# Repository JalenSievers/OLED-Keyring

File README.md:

# OLED-Keyring
A custom-designed OLED keyring featuring an ATmega4808 microcontroller, compact PCB, and embedded firmware for displaying personalised messages and simple games.

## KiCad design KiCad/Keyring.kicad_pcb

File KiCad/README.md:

KiCad schematic and PCB design files for the OLED keyring project.

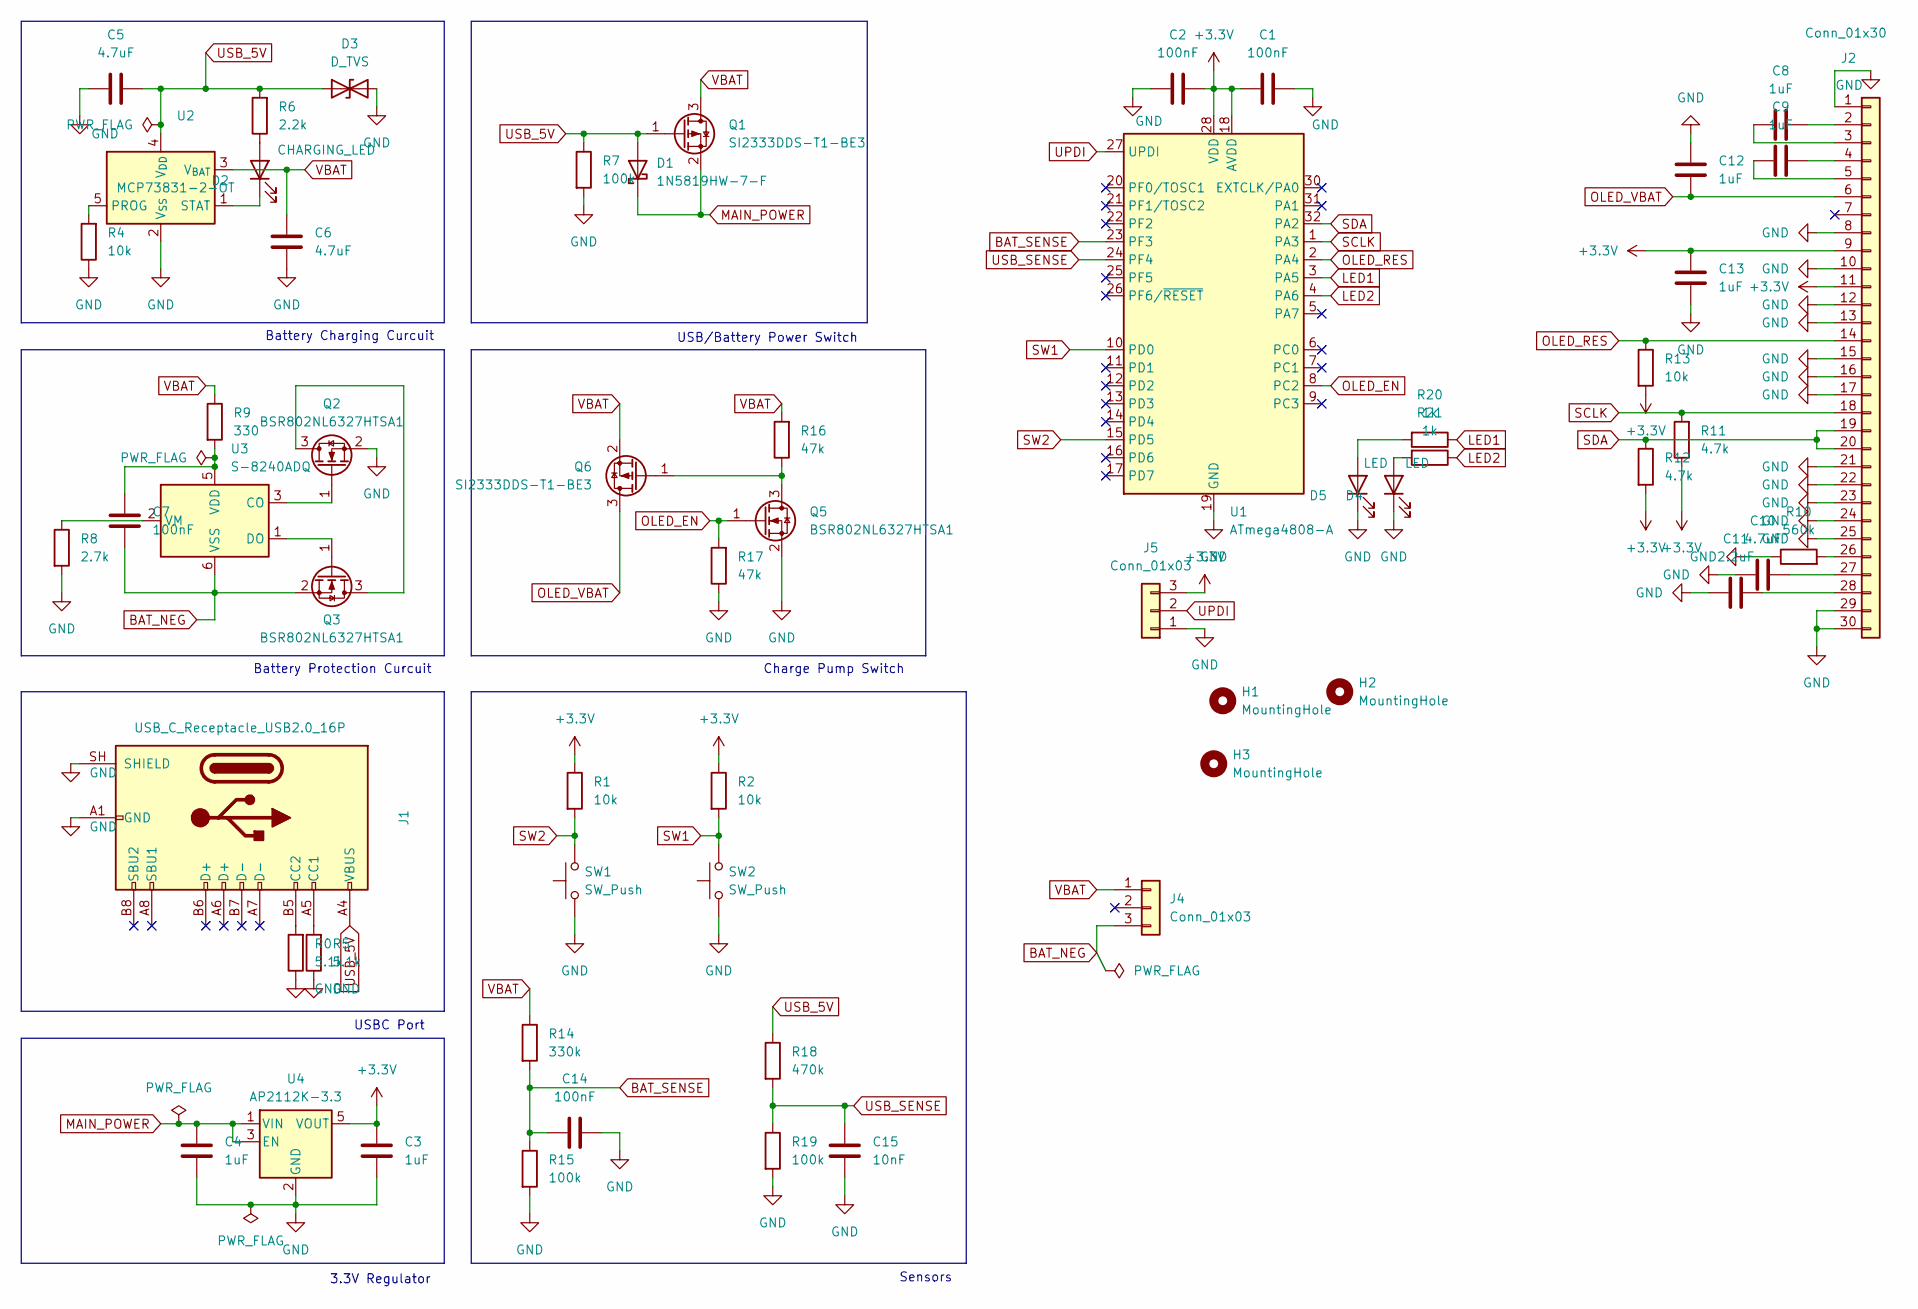
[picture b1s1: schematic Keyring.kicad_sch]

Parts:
C1, C2, C7, C14: 100nF; C_0805_2012Metric_Pad1.18x1.45mm_HandSolder
C3, C4, C8, C9, C12, C13: 1uF; C_0805_2012Metric_Pad1.18x1.45mm_HandSolder
C5, C6: 4.7uF; C_0805_2012Metric_Pad1.18x1.45mm_HandSolder
C10: 4.7uF; C_0805_2012Metric_Pad1.18x1.45mm_HandSolder; Voltage 16V
C11: 2.2uF; C_0805_2012Metric_Pad1.18x1.45mm_HandSolder; Voltage 16V
C15: 10nF; C_0805_2012Metric_Pad1.18x1.45mm_HandSolder
D1: 1N5819HW-7-F; D_SOD-123
D2: CHARGING_LED; LED_0805_2012Metric_Pad1.15x1.40mm_HandSolder
D3: D_TVS; D_SOD-123F
D4, D5: LED; LED_0805_2012Metric_Pad1.15x1.40mm_HandSolder
H1, H2, H3: MountingHole; MountingHole_3.2mm_M3
J1: USB_C_Receptacle_USB2.0_16P; USB_C_Receptacle_GCT_USB4110
J2: Conn_01x30; FPC_30
J4: Conn_01x03; Battery
J5: Conn_01x03; Programming
Q1, Q6: SI2333DDS-T1-BE3; SOT-23_Handsoldering
Q2, Q3, Q5: BSR802NL6327HTSA1; SOT-23_Handsoldering
R0, R5: 5.1k; R_0805_2012Metric_Pad1.20x1.40mm_HandSolder
R1, R2, R4, R13: 10k; R_0805_2012Metric_Pad1.20x1.40mm_HandSolder
R6: 2.2k; R_0805_2012Metric_Pad1.20x1.40mm_HandSolder
R7, R15, R19: 100k; R_0805_2012Metric_Pad1.20x1.40mm_HandSolder
R8: 2.7k; R_0805_2012Metric_Pad1.20x1.40mm_HandSolder
R9: 330; R_0805_2012Metric_Pad1.20x1.40mm_HandSolder
R10: 560k; R_0805_2012Metric_Pad1.20x1.40mm_HandSolder
R11, R12: 4.7k; R_0805_2012Metric_Pad1.20x1.40mm_HandSolder
R14: 330k; R_0805_2012Metric_Pad1.20x1.40mm_HandSolder
R16, R17: 47k; R_0805_2012Metric_Pad1.20x1.40mm_HandSolder
R18: 470k; R_0805_2012Metric_Pad1.20x1.40mm_HandSolder
R20, R21: 1k; R_0805_2012Metric_Pad1.20x1.40mm_HandSolder
SW1, SW2: SW_Push; SW_SPST_PTS645Sx43SMTR92
U1: ATmega4808-A; TQFP-32_7x7mm_P0.8mm
U2: MCP73831-2-OT; SOT-23-5
U3: S-8240ADQ; SOT-23-6
U4: AP2112K-3.3; SOT-23-5

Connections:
+3.3V: C1.1, C2.2, C3.1, C13.2, J2.9, J2.11, J5.3, R1.1, R2.1, R11.1, R12.2, R13.2, U1.18 (AVDD), U1.28 (VDD), U4.5 (VOUT)
BAT_NEG: C7.2, J4.3, Q3.2 (S), U3.6 (VSS)
BAT_SENSE: C14.1, R14.2, R15.1, U1.23 (PF3)
GND: C1.2, C2.1, C3.2, C4.2, C5.1, C6.1, C10.1, C11.1, C12.2, C13.1, C14.2, C15.1, D3.2 (A2), D4.1 (K), D5.1 (K), J1.A1 (GND), J1.A12 (GND), J1.B1 (GND), J1.B12 (GND), J1.SH (SHIELD), J2.1, J2.8, J2.10, J2.12, J2.13, J2.15, J2.16, J2.17, J2.21, J2.22, J2.23, J2.24, J2.25, J2.29, J2.30, J5.1, Q2.2 (S), Q5.2 (S), R0.1, R4.1, R5.1, R7.2, R8.2, R10.1, R15.2, R17.1, R19.2, SW1.1, SW2.1, U1.19 (GND), U1.29 (GND), U2.2 (V_{SS}), U4.2 (GND)
LED1: R20.1, U1.3 (PA5)
LED2: R21.1, U1.4 (PA6)
MAIN_POWER: C4.1, D1.1 (K), Q1.2 (S), U4.1 (VIN), U4.3 (EN)
unnamed: D2.2 (A), R6.1
unnamed: D2.1 (K), U2.1 (STAT)
unnamed: D4.2 (A), R21.2
unnamed: D5.2 (A), R20.2
unnamed: J1.A5 (CC1), R5.2
unnamed: J1.B5 (CC2), R0.2
unnamed: C8.2, J2.2
unnamed: C8.1, J2.3
unnamed: C9.2, J2.4
unnamed: C9.1, J2.5
unnamed: J2.26, R10.2
unnamed: C10.2, J2.27
unnamed: C11.2, J2.28
unnamed: Q2.3 (D), Q3.3 (D)
unnamed: Q2.1 (G), U3.3 (CO)
unnamed: Q3.1 (G), U3.1 (DO)
unnamed: Q5.3 (D), Q6.1 (G), R16.1
unnamed: R4.2, U2.5 (PROG)
unnamed: C7.1, R9.2, U3.5 (VDD)
unnamed: R8.1, U3.2 (VM)
OLED_EN: Q5.1 (G), R17.2, U1.8 (PC2)
OLED_RES: J2.14, R13.1, U1.2 (PA4)
OLED_VBAT: C12.1, J2.6, Q6.3 (D)
SCLK: J2.18, R11.2, U1.1 (PA3)
SDA: J2.19, J2.20, R12.1, U1.32 (PA2)
SW1: R2.2, SW2.2, U1.10 (PD0)
SW2: R1.2, SW1.2, U1.15 (PD5)
UPDI: J5.2, U1.27 (UPDI)
USB_5V: C5.2, D1.2 (A), D3.1 (A1), J1.A4 (VBUS), J1.A9 (VBUS), J1.B4 (VBUS), J1.B9 (VBUS), Q1.1 (G), R6.2, R7.1, R18.1, U2.4 (V_{DD})
USB_SENSE: C15.2, R18.2, R19.1, U1.24 (PF4)
VBAT: C6.2, J4.1, Q1.3 (D), Q6.2 (S), R9.1, R14.1, R16.2, U2.3 (V_{BAT})

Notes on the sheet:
USB/Battery Power Switch
Battery Protection Curcuit
Sensors
Battery Charging Curcuit
Charge Pump Switch
USBC Port
3.3V Regulator

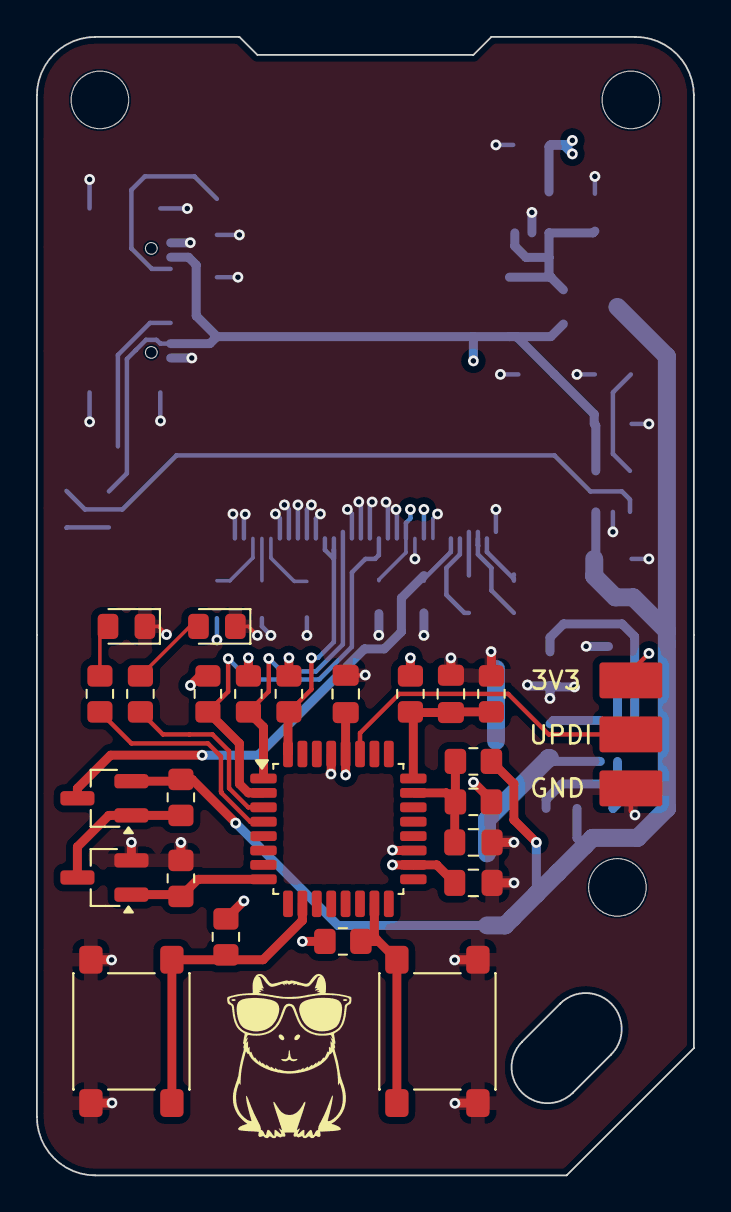
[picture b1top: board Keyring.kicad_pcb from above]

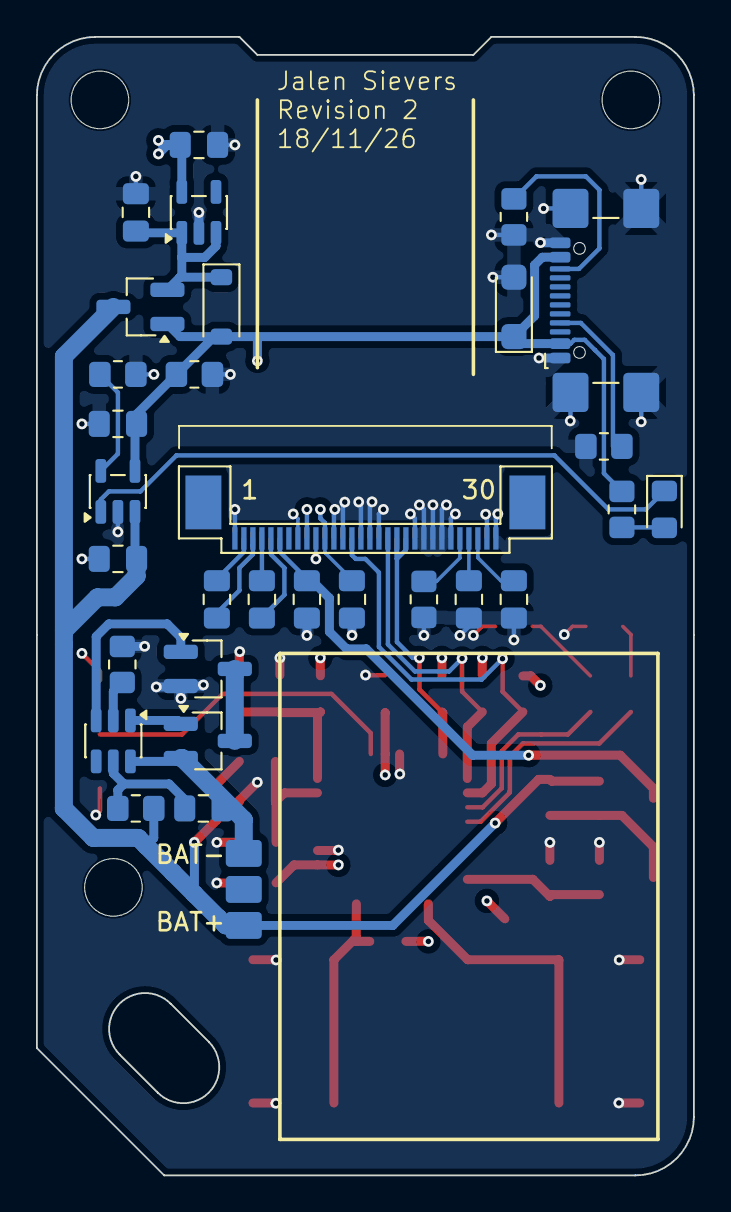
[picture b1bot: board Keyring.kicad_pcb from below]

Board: 4 copper layers, 36.5 x 63.2 mm, 59 parts (31 on the bottom side), 38 nets.
